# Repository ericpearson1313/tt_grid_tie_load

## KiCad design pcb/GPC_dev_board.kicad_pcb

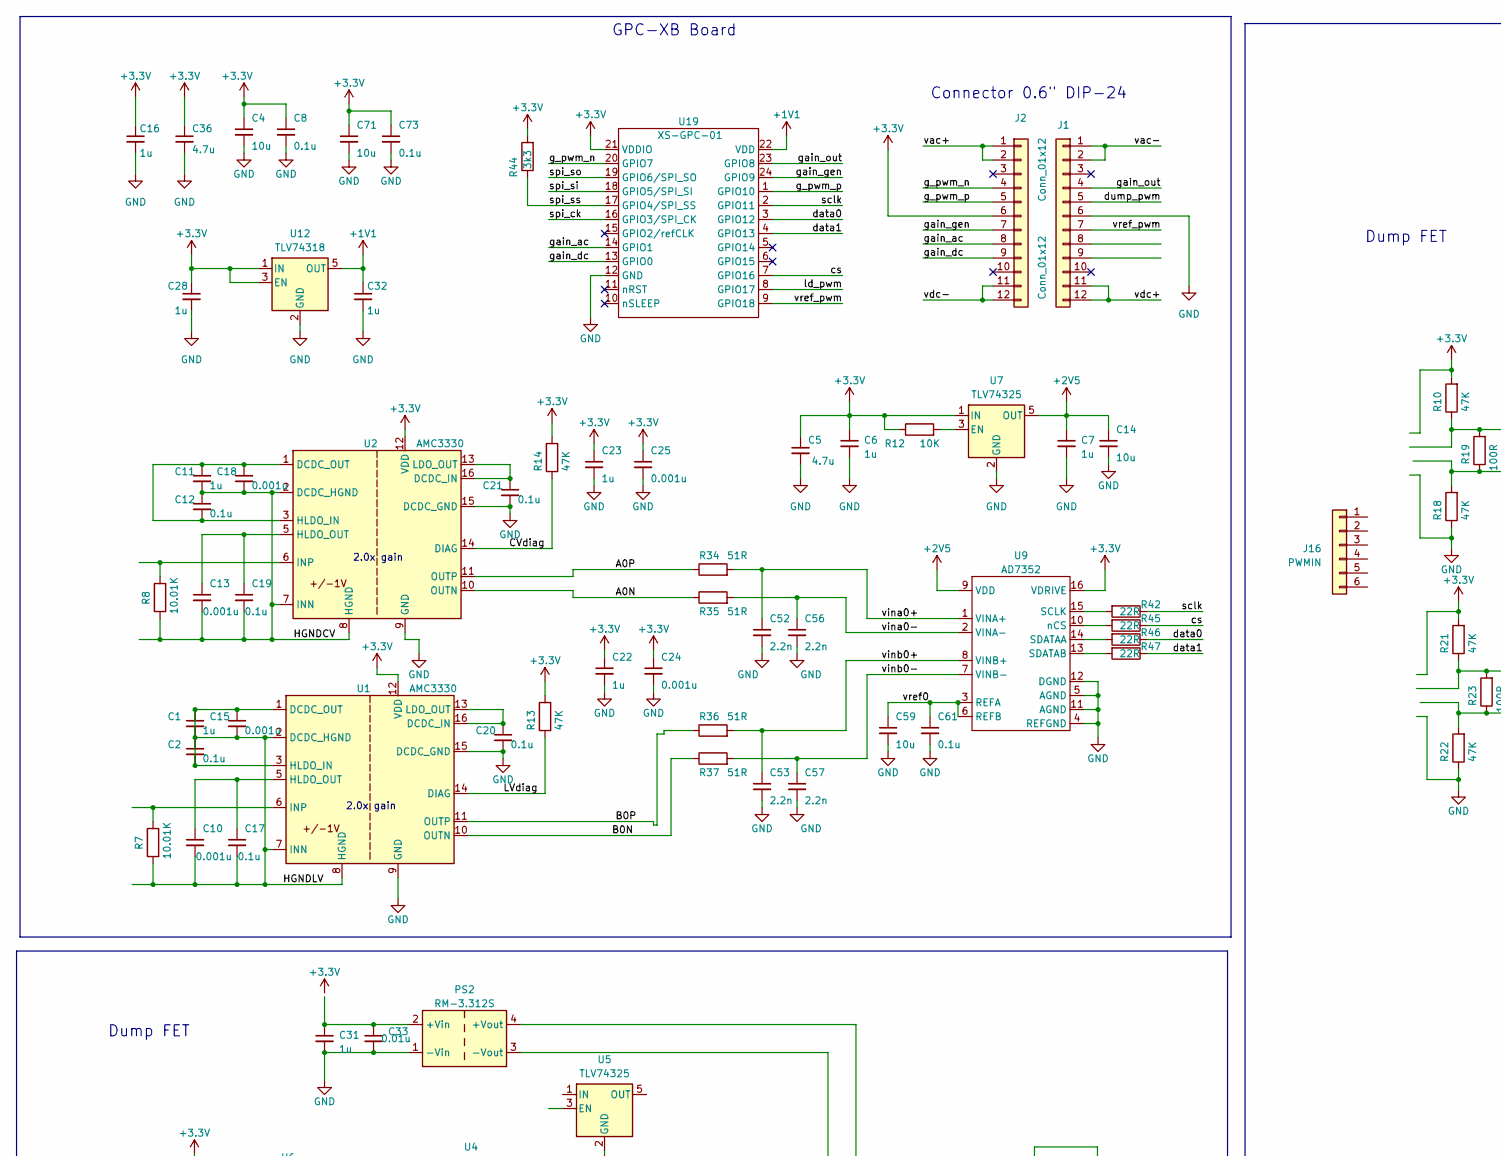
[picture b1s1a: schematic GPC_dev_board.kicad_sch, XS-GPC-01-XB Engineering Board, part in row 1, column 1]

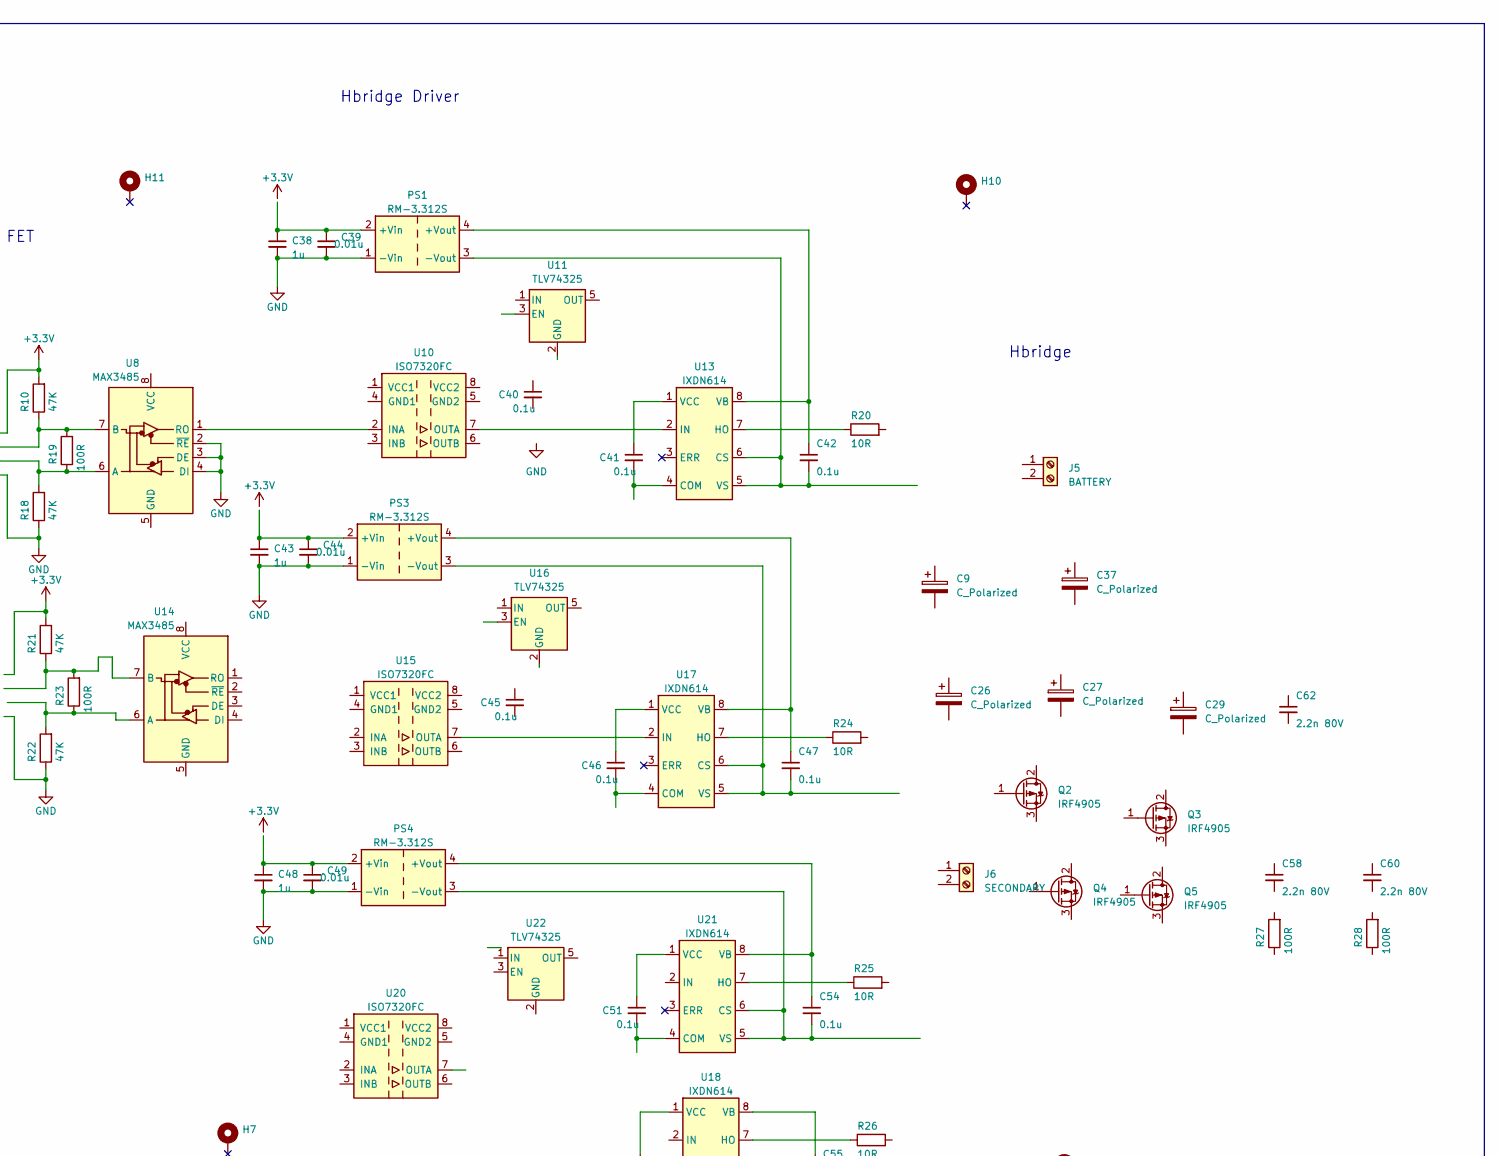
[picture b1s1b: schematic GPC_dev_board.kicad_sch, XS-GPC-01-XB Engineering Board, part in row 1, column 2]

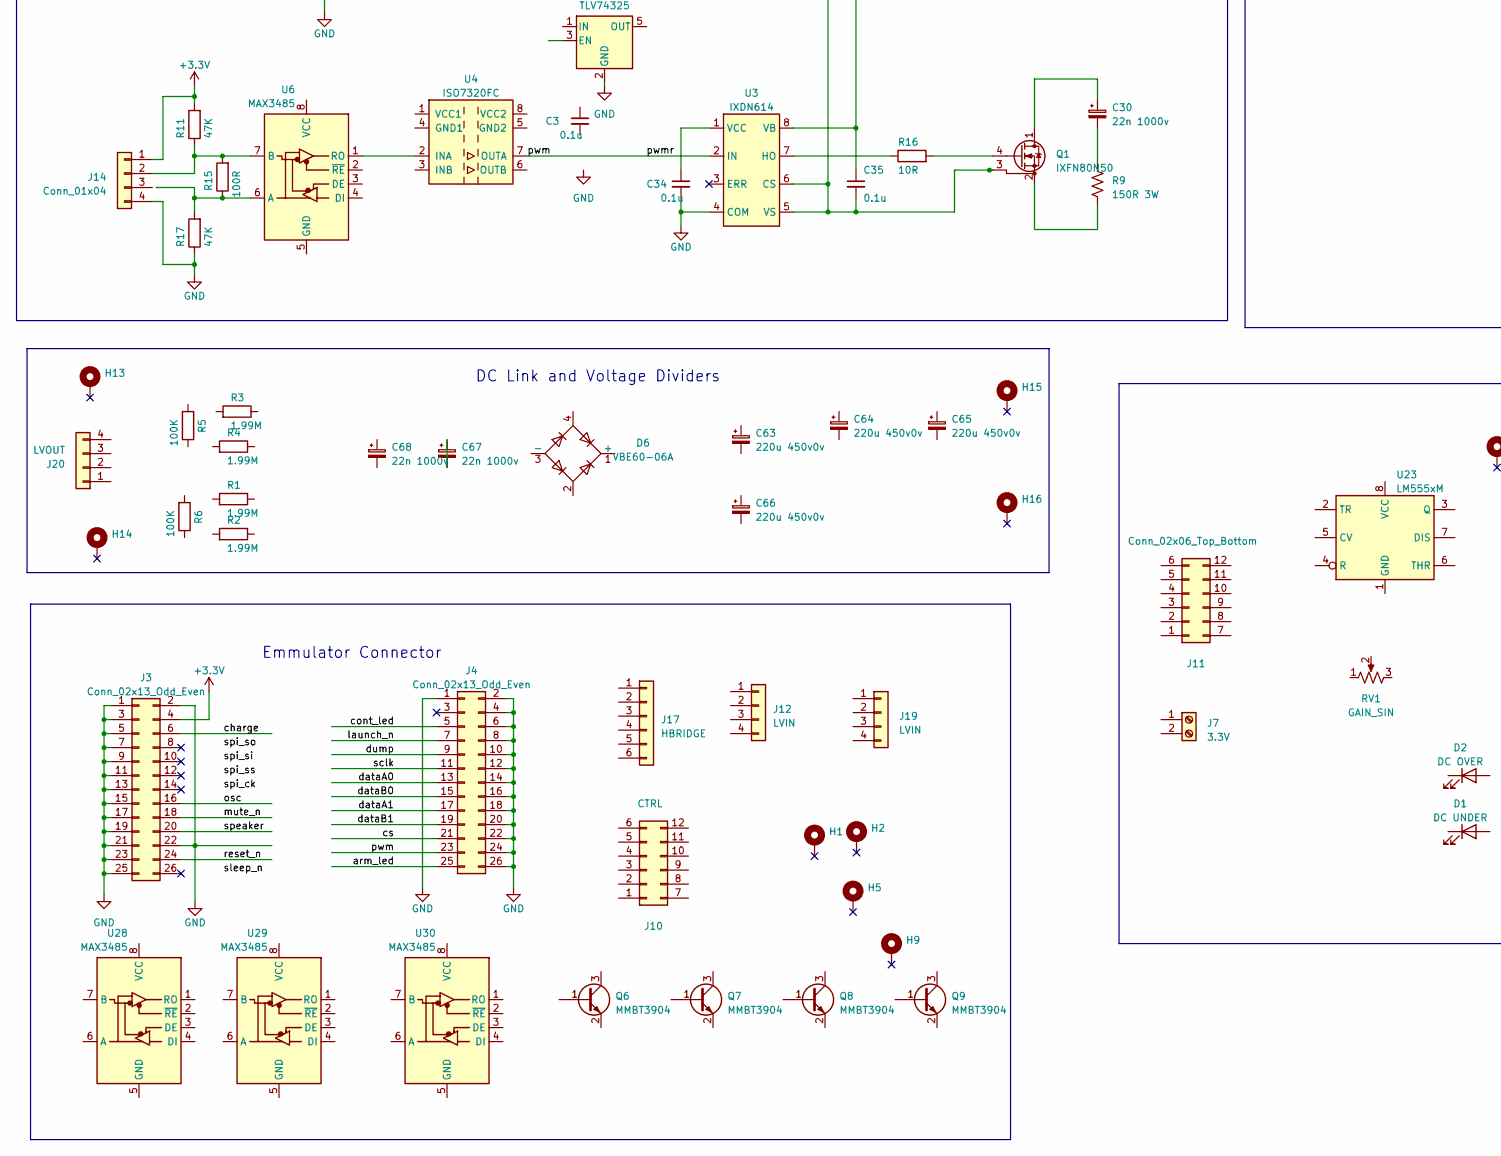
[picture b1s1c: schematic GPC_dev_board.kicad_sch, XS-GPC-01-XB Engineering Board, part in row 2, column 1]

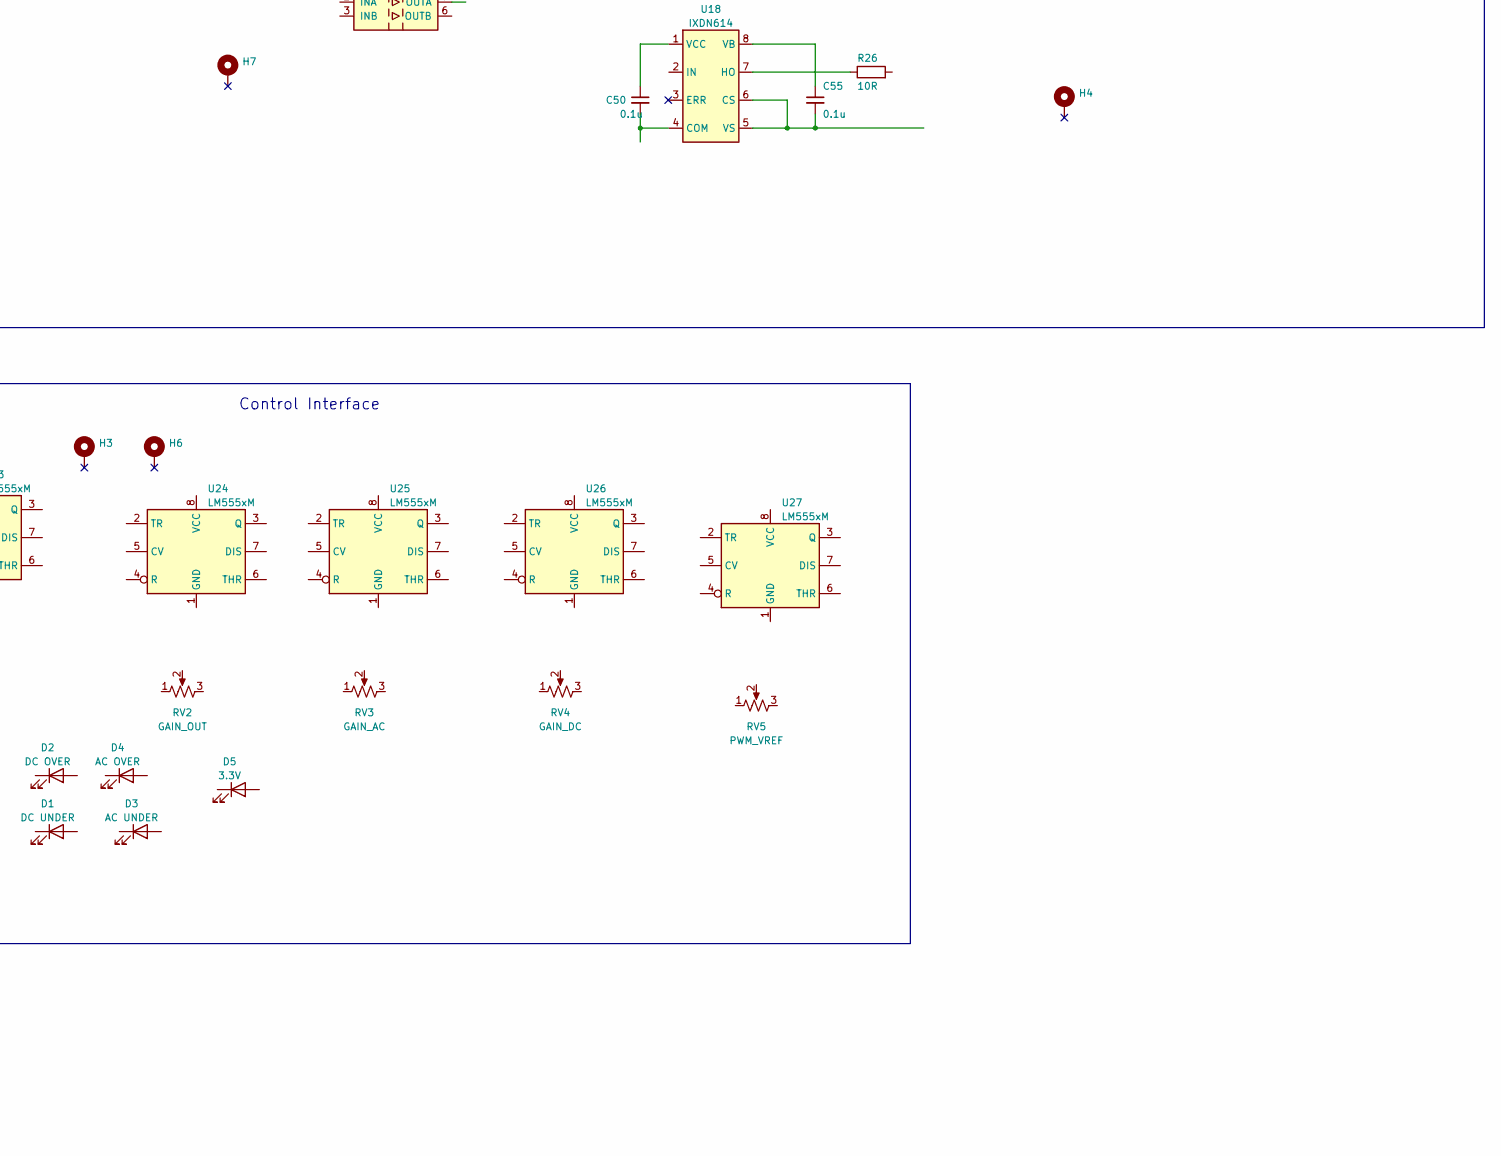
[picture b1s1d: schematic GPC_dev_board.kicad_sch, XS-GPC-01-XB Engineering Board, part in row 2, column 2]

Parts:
C1, C6, C7, C11, C16, C22, C23, C28, C31, C32, C38, C43, C48: 1u; C_0603_1608Metric
C2, C3, C8, C12, C17, C19, C20, C21, C34, C35, C40, C41, C42, C45, C46, C47, C50, C51, C54, C55, C61, C73: 0.1u; C_0603_1608Metric
C4, C14, C59, C71: 10u; C_1206_3216Metric
C5, C36: 4.7u; C_1206_3216Metric
C9, C26, C27, C29, C37: C_Polarized; CP_Radial_D10.0mm_P5.00mm
C10, C13, C15, C18, C24, C25: 0.001u; C_0603_1608Metric
C30, C67, C68: 22n 1000v; C_Rect_L13.0mm_W6.0mm_P10.00mm_FKS3_FKP3_MKS4
C33, C39, C44, C49: 0.01u; C_0603_1608Metric
C52, C53, C56, C57: 2.2n; C_0603_1608Metric
C58, C60, C62: 2.2n 80V; C_0603_1608Metric
C63, C64, C65, C66: 220u 450v0v; CP_Radial_D18.0mm_P7.50mm
D1: DC UNDER; LED_0603_1608Metric
D2: DC OVER; LED_0603_1608Metric
D3: AC UNDER; LED_0603_1608Metric
D4: AC OVER; LED_0603_1608Metric
D5: 3.3V; LED_0603_1608Metric
D6: VBE60-06A; SOT-227
H1, H2, H3, H4, H5, H6, H7, H9, H10, H11, H13, H14, H15, H16: MountingHole_3mm_Pad
J1, J2: Conn_01x12; PinHeader_1x12_P2.54mm_Vertical
J3, J4: Conn_02x13_Odd_Even; PinSocket_2x13_P2.54mm_Vertical
J5: BATTERY; TerminalBlock_Phoenix_MKDS-1,5-2-5.08_1x02_P5.08mm_Horizont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
J6: SECONDARY; TerminalBlock_Phoenix_MKDS-1,5-2-5.08_1x02_P5.08mm_Horizont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
J7: 3.3V; TerminalBlock_Phoenix_MKDS-1,5-2-5.08_1x02_P5.08mm_Horizont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
J10: CTRL; PinHeader_2x06_P2.54mm_Vertical
J11: Conn_02x06_Top_Bottom; PinHeader_2x06_P2.54mm_Horizontal
J12, J19: LVIN; PinHeader_1x04_P2.54mm_Vertical
J14: Conn_01x04; PinHeader_1x04_P2.54mm_Horizontal
J16: PWMIN; PinHeader_1x06_P2.54mm_Horizontal
J17: HBRIDGE; PinHeader_1x06_P2.54mm_Vertical
J20: LVOUT; PinHeader_1x04_P2.54mm_Horizontal
PS1, PS2, PS3, PS4: RM-3.312S; Converter_DCDC_Murata_MEE1SxxxxSC_THT
Q1: IXFN80N50; SOT-227
Q2, Q3, Q4, Q5: IRF4905; TO-220-3_Horizontal_TabDown
Q6, Q7, Q8, Q9: MMBT3904; SOT-23
R1, R2, R3, R4: 1.99M; R_2512_6332Metric; JLC C778416
R5, R6: 100K; R_2512_6332Metric; JLC C778416
R7, R8: 10.01K; R_0603_1608Metric; JLC C778416
R9: 150R 3W; R_2512_6332Metric
R10, R11, R13, R14, R17, R18, R21, R22: 47K; R_0603_1608Metric; JLC C778416
R12: 10K; R_0603_1608Metric; JLC C778416
R15, R19, R23, R27, R28: 100R; R_0603_1608Metric; JLC C778416
R16, R20, R24, R25, R26: 10R; R_0603_1608Metric; JLC C778416
R34, R35, R36, R37: 51R; R_0603_1608Metric; JLC C778416
R42, R45, R46, R47: 22R; R_0603_1608Metric; JLC C319967
R44: 3k3; R_0603_1608Metric; JLC C319967
RV1: GAIN_SIN; Potentiometer_Bourns_3299X_Horizontal
RV2: GAIN_OUT; Potentiometer_Bourns_3299X_Horizontal
RV3: GAIN_AC; Potentiometer_Bourns_3299X_Horizontal
RV4: GAIN_DC; Potentiometer_Bourns_3299X_Horizontal
RV5: PWM_VREF; Potentiometer_Bourns_3299X_Horizontal
U1, U2: AMC3330; SOIC-16W_7.5x10.3mm_P1.27mm
U3, U13, U17, U18, U21: IXDN614; SOIC-8_3.9x4.9mm_P1.27mm
U4, U10, U15, U20: ISO7320FC; SOIC-8_3.9x4.9mm_P1.27mm
U5, U7, U11, U16, U22: TLV74325; SOT-23-5
U6, U8, U14, U28, U29, U30: MAX3485; SOIC-8_3.9x4.9mm_P1.27mm
U9: AD7352; TSSOP-16_4.4x5mm_P0.65mm
U12: TLV74318; SOT-23-5
U19: XS-GPC-01; QFN-24-3x3mm
U23, U24, U25, U26, U27: LM555xM; SOIC-8_3.9x4.9mm_P1.27mm

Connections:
+1V1: C32.1, U12.5 (OUT), U19.22 (VDD)
+2V5: C7.1, C14.1, U7.5 (OUT), U9.9 (VDD)
+3.3V: C4.1, C5.1, C6.1, C8.1, C16.1, C22.1, C23.1, C24.1, C25.1, C28.1, C36.1, C71.1, C73.1, J2.6, J3.4, J14.1, R10.2, R11.2, R12.1, R13.2, R14.2, R21.2, R44.2, U1.12 (VDD), U2.12 (VDD), U7.1 (IN), U9.16 (VDRIVE), U12.1 (IN), U12.3 (EN), U19.21 (VDDIO)
/A0N: R35.1, U2.10 (OUTN)
/A0P: R34.1, U2.11 (OUTP)
/B0N: R37.1, U1.10 (OUTN)
/B0P: R36.1, U1.11 (OUTP)
/CVdiag: R14.1, U2.14 (DIAG)
/HGNDCV: C11.2, C12.1, C13.2, C18.2, C19.2, R8.1, U2.2 (DCDC_HGND), U2.7 (INN), U2.8 (HGND)
/HGNDLV: C1.1, C1.2, C2.1, C2.2, C10.2, C15.1, C15.2, C17.2, R7.1, U1.1 (DCDC_OUT), U1.2 (DCDC_HGND), U1.3 (HLDO_IN), U1.7 (INN), U1.8 (HGND)
/LVdiag: R13.1, U1.14 (DIAG)
/arm_led: J4.25
/charge: J3.6
/cont_led: J4.5
/cs: J4.21, R45.1, U19.7 (GPIO16)
/data0: R46.1, U19.3 (GPIO12)
/data1: R47.1, U19.4 (GPIO13)
/dataA0: J4.13
/dataA1: J4.17
/dataB0: J4.15
/dataB1: J4.19
/dump: J4.9
/dump_pwm: J1.5
/g_pwm_n: J2.4, U19.20 (GPIO7)
/g_pwm_p: J2.5, U19.1 (GPIO10)
/gain_ac: J2.8, U19.14 (GPIO1)
/gain_dc: J2.9, U19.13 (GPIO0)
/gain_gen: J2.7, U19.24 (GPIO9)
/gain_out: J1.4, U19.23 (GPIO8)
/launch_n: J4.7
/ld_pwm: U19.8 (GPIO17)
/mute_n: J3.18
/osc: J3.16
/pwm: J4.23, U4.7 (OUTA)
/reset_n: J3.24
/sclk: J4.11, R42.1, U19.2 (GPIO11)
/speaker: J3.20
/spi_ck: U19.16 (GPIO3/SPI_CK)
/spi_si: U19.18 (GPIO5/SPI_SI)
/spi_so: U19.19 (GPIO6/SPI_SO)
/spi_ss: R44.1, U19.17 (GPIO4/SPI_SS)
/vac+: J2.1, J2.2
/vac-: J1.1, J1.2
/vdc+: J1.11, J1.12
/vdc-: J2.11, J2.12
/vina0+: C52.1, R34.2, U9.1 (VINA+)
/vina0-: C56.1, R35.2, U9.2 (VINA-)
/vinb0+: C53.1, R36.2, U9.8 (VINB+)
/vinb0-: C57.1, R37.2, U9.7 (VINB-)
/vref0: C59.1, C61.1, U9.3 (REFA), U9.6 (REFB)
/vref_pwm: J1.7, U19.9 (GPIO18)
GND: C4.2, C5.2, C6.2, C7.2, C8.2, C14.2, C16.2, C20.2, C21.2, C22.2, C23.2, C24.2, C25.2, C28.2, C31.2, C32.2, C33.2, C34.2, C36.2, C38.2, C39.2, C43.2, C44.2, C48.2, C49.2, C52.2, C53.2, C56.2, C57.2, C59.2, C61.2, C71.2, C73.2, J1.6, J3.1, J3.2, J3.3, J3.5, J3.7, J3.9, J3.11, J3.13, J3.15, J3.17, J3.19, J3.21, J3.22, J3.23, J3.25, J4.1, J4.2, J4.4, J4.6, J4.8, J4.10, J4.12, J4.14, J4.16, J4.18, J4.20, J4.22, J4.24, J4.26, J14.4, PS1.1 (-Vin), PS2.1 (-Vin), PS3.1 (-Vin), PS4.1 (-Vin), R17.1, R18.1, R22.1, U1.9 (GND), U1.15 (DCDC_GND), U2.9 (GND), U2.15 (DCDC_GND), U5.2 (GND), U7.2 (GND), U8.2 (~RE), U8.3 (DE), U8.4 (DI), U9.4 (REFGND), U9.5 (AGND), U9.11 (AGND), U9.12 (DGND), U12.2 (GND), U19.12 (GND)
unnamed: C30.2, R9.1
unnamed: C67.1, C67.2
unnamed: J14.2, R11.1, R15.2, U6.7 (B)
unnamed: C38.1, C39.1, PS1.2 (+Vin)
unnamed: C42.1, PS1.4 (+Vout)
unnamed: C42.2, PS1.3 (-Vout)
unnamed: C31.1, C33.1, PS2.2 (+Vin)
unnamed: C35.1, PS2.4 (+Vout)
unnamed: C35.2, PS2.3 (-Vout), Q1.3 (DS)
unnamed: C43.1, C44.1, PS3.2 (+Vin)
unnamed: C47.1, PS3.4 (+Vout)
unnamed: C47.2, PS3.3 (-Vout)
unnamed: C48.1, C49.1, PS4.2 (+Vin)
unnamed: C54.1, PS4.4 (+Vout)
unnamed: C54.2, PS4.3 (-Vout)
unnamed: C30.1, Q1.1 (D)
unnamed: Q1.4 (G), R16.2
unnamed: Q1.2 (S), R9.2
unnamed: C20.1, U1.13 (LDO_OUT), U1.16 (DCDC_IN)
unnamed: C10.1, C17.1, U1.5 (HLDO_OUT)
unnamed: R7.2, U1.6 (INP)
unnamed: C21.1, U2.13 (LDO_OUT), U2.16 (DCDC_IN)
unnamed: C11.1, C12.2, C18.1, U2.1 (DCDC_OUT), U2.3 (HLDO_IN)
unnamed: C13.1, C19.1, U2.5 (HLDO_OUT)
unnamed: R8.2, U2.6 (INP)
unnamed: U4.2 (INA), U6.1 (RO)
unnamed: R15.1, R17.2, U6.6 (A)
unnamed: R12.2, U7.3 (EN)
unnamed: R18.2, R19.1, U8.6 (A)
unnamed: R10.1, R19.2, U8.7 (B)
unnamed: R42.2, U9.15 (SCLK)
unnamed: R46.2, U9.14 (SDATAA)
unnamed: R47.2, U9.13 (SDATAB)
unnamed: R45.2, U9.10 (nCS)
unnamed: U8.1 (RO), U10.2 (INA)
unnamed: R22.2, R23.1, U14.6 (A)
unnamed: R21.1, R23.2, U14.7 (B)

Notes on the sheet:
Connector 0.6" DIP-24
GPC-XB Board
Dump FET
2.0x gain
DC Link and Voltage Dividers
Hbridge Driver
Control Interface
Emmulator Connector
Hbridge

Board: 6 copper layers, 194 parts (20 on the bottom side), 71 nets, no tracks yet.

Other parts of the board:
C64#2, C64#3, C64#4, C64#5, C64#6, C64#7, C64#8: 220u 450v0v; CP_Radial_D18.0mm_P7.50mm

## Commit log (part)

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2026-05-25 Updated yaml and tt_um_
2026-05-25 getting flow running?
2026-05-26 boiler plate sim running, linked in cordic
2026-05-26 109% utilization, move to a 1x2, we still have ADC logic to add
2026-05-26 very fine 20ns pwm edge res, and top level basic test on 1 cycle
2026-05-29 Kept the linear and removed the bang-bang controller. 1x1?
2026-05-29 Tie off unused output
2026-05-30 Updated TB with packed pinout
2026-05-30 1x1 Fit test
2026-05-30 1x1 failed p&r at 87.5%, back to 1x2 at 42%, sigh
2026-06-01 Add Vref pwm input for DC loop
2026-06-02 need sim model in tb for GL sims
2026-06-03 2x2 maybe needed?
2026-06-03 Draft datasheet and quick forge port (105%), will update as progress
2026-06-03 bring forge-ified blocs back to tt, help keep in sync
2026-06-07 Updated forge code, fixup, in sync but 105% util
2026-06-07 AC desable on large undervoltage, Thresh logic opt
2026-06-07 port/copy asic->fpga flow 94%
2026-06-08 Try a 1x1
2026-06-08 remove dc_delta ff regs to save some gates
2026-06-08 remove few more flops
2026-06-08 put absin reg back in without reset
2026-06-08 final 1x1 try
2026-06-09 Revise documentation for ASIC features and specifications
    Updated the documentation to reflect changes in sensing capabilities, control loops, and input/output specifications. Improved clarity and accuracy of descriptions regarding the ASIC's functionality 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
2026-06-09 Add tb pwm and cordic, datapath fully running, replicate cordic.v for GL sims
2026-06-09 clean up ac wave
2026-06-11 Added model cipping, tweaked gains, stabilizes in 13 cycles
2026-06-13 Add diagrams to info.md
2026-06-13 Fix markdown image syntax in info.md
    Corrected image markdown syntax for block and system diagrams in the documentation.
2026-06-15 Test FPGA: Integrated Dc link model and cordic together for AC, DC response to push back against chip
2026-06-15 conditional FPGA probes inside TT, got chip video connected and can see/zoom 60 Hz Vac. capture/monitor 5 signed and 8 binary signals.
2026-06-15 Added Text overlay for analog channels
2026-06-16 Fix fast_acc clipping
2026-06-16 Restore in-control range for system test
2026-06-16 FPGA sims running with HDMI wave display. Still some work though
2026-06-16 fpga simulation environment running at 1d23834
2026-06-17 FPGA sim fixes (wiring) and ADC simulator external pads, single 1.3s run with capture power steps of 100W each 1/4 sec.
2026-06-17 Tighten dc acc -ve limit and dc low signalling
2026-06-18 Fix flops to use nonblocking <=
2026-06-18 Simulation FPGA re-order sections and added 2nd test (dc gain ramp to tighten Vdc envelope (`ifdef to select test for now)
2026-06-18 Update forge to current TT (with cordic!)
2026-06-21 Development board for chip bringup thinking added to datasheet.
2026-06-22 Early rough kicad project and initial floorplan of development board
